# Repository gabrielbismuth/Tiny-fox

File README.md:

# Tiny-fox
Descripción del Proyecto Este repositorio contiene los archivos de diseño de una placa de circuito impreso (PCB) basada en el ESP32 Pico D4. La PCB ha sido diseñada con el objetivo de proporcionar una plataforma flexible y de código abierto para proyectos de IoT, desarrollo de productos y prototipado rápido.

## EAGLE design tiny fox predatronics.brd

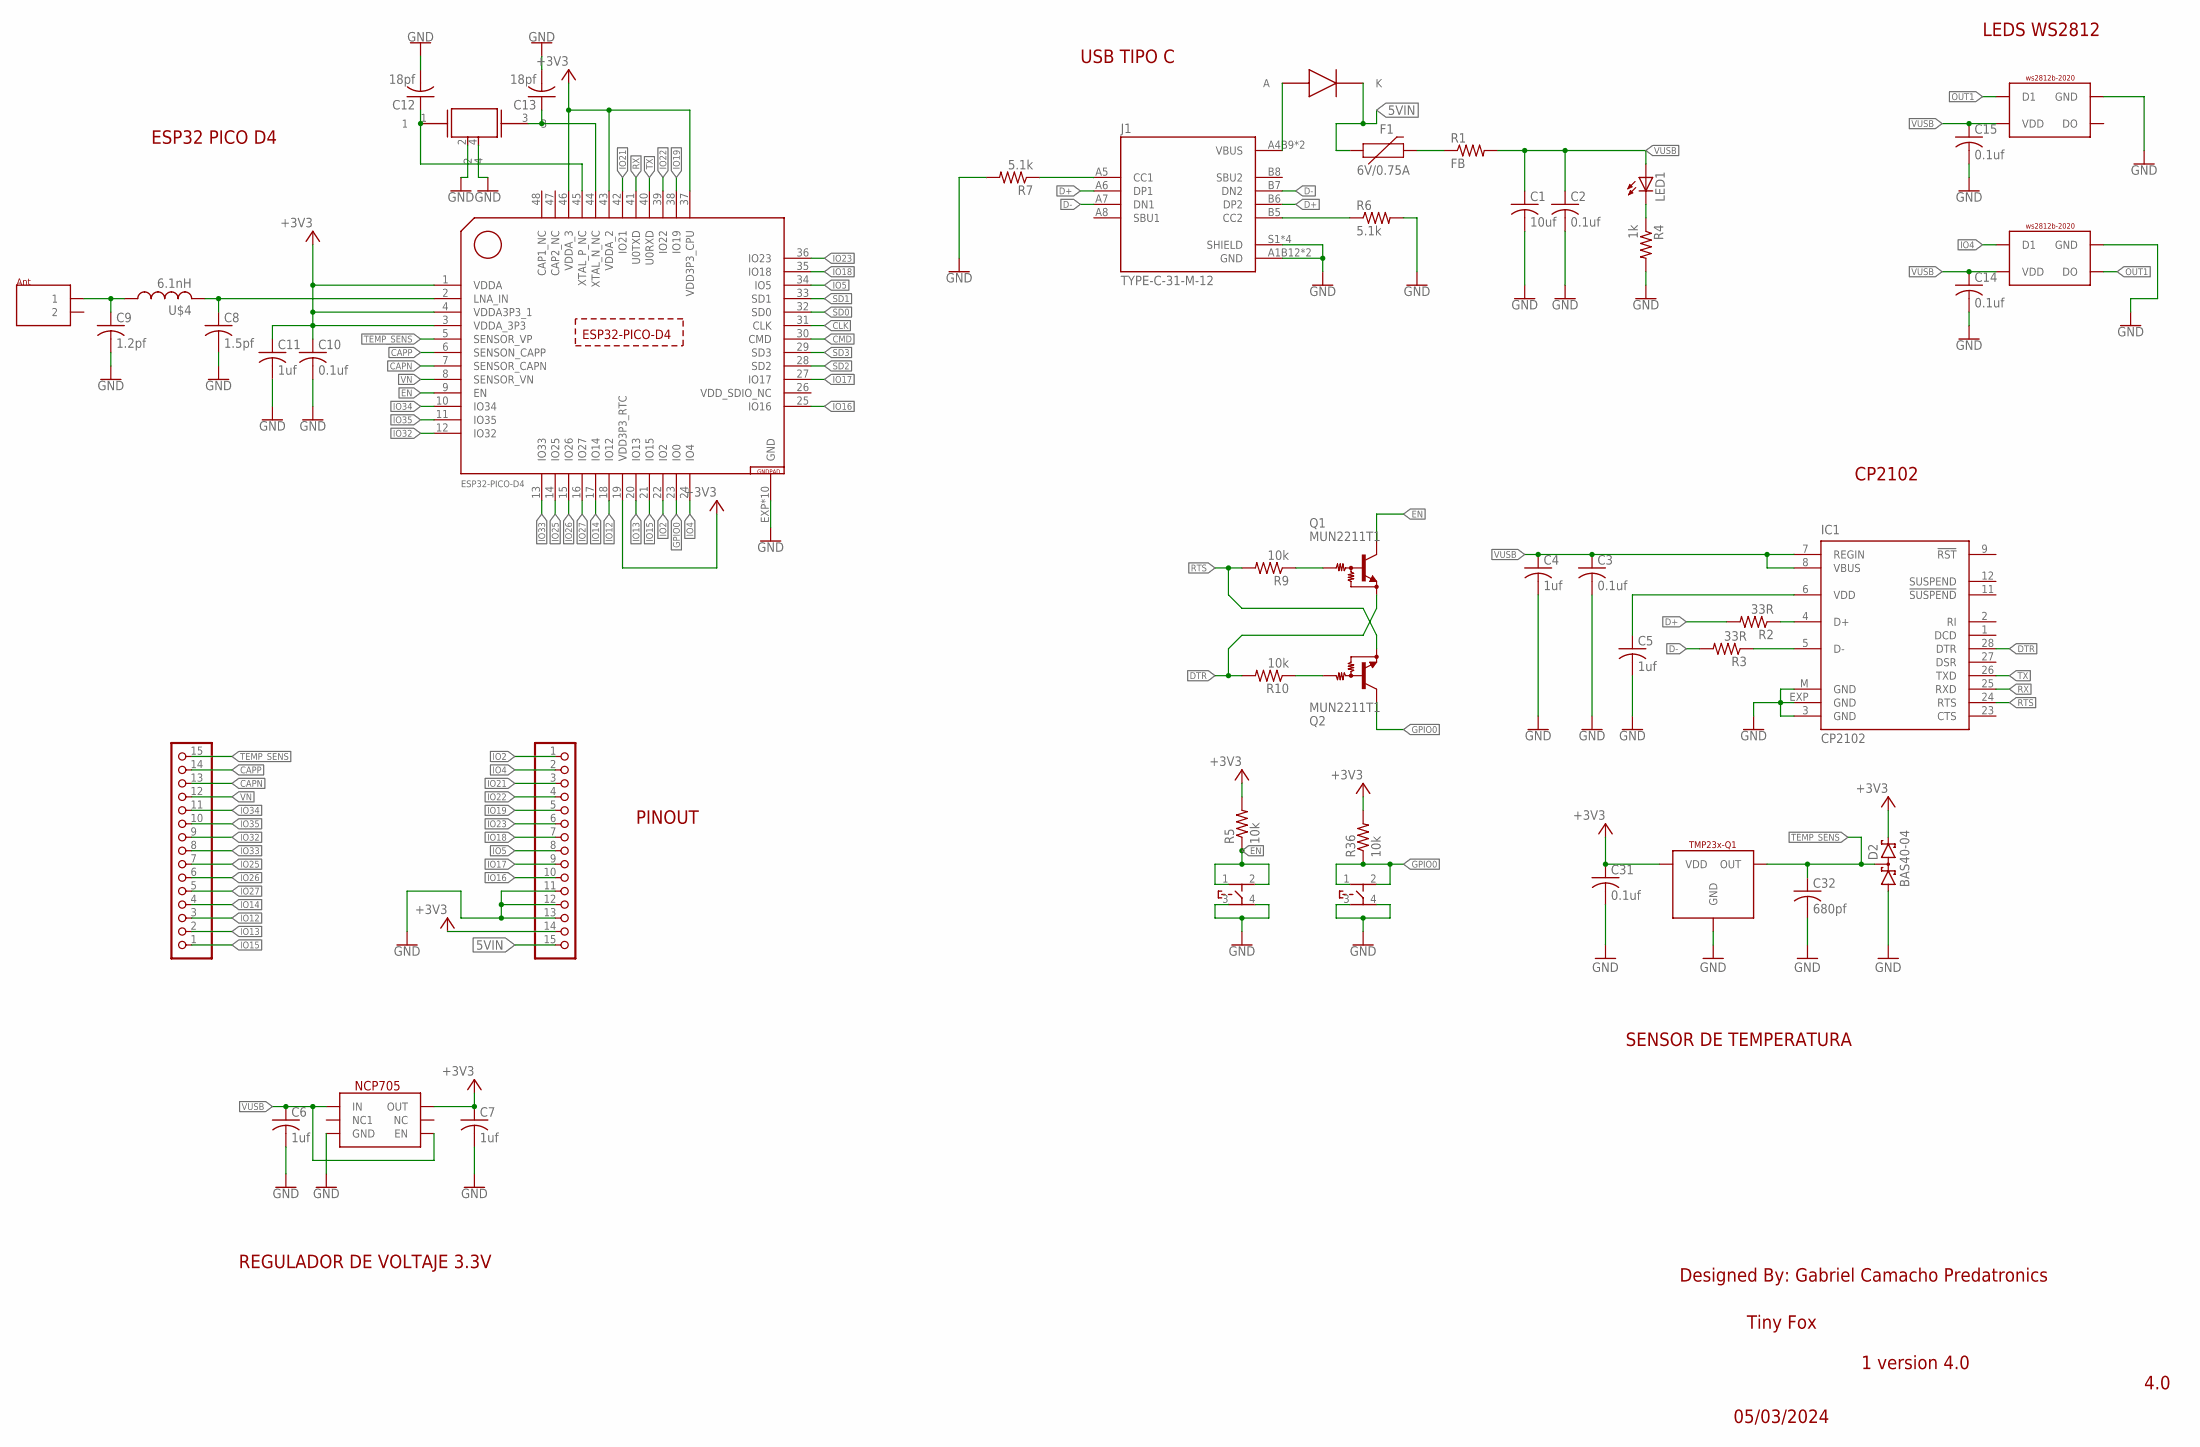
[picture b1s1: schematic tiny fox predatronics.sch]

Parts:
C1: 10uf; C0805
C2, C3, C10, C14, C15, C31: 0.1uf; C0603
C4, C5, C6, C7, C11: 1uf; C0603
C8: 1.5pf; C0402
C9: 1.2pf; C0402
C12, C13: 18pf; C0603
C32: 680pf; C0603
D2: BAS40-04; SOT23
F1: 6V/0.75A; 1206
IC1: CP2102; MLP28
J1: TYPE-C-31-M-12; HRO_TYPE-C-31-M-12
JP1, JP2: PINHD-1X15; 1X15
LED1: LEDCHIPLED_0603; CHIPLED_0603
Q1, Q2: MUN2211T1; SC59-BEC
R1: FB; R0805
R2, R3: 33R; R0603
R4: 1k; R0603
R5, R9, R10, R36: 10k; R0603
R6, R7: 5.1k; R0402
U$1: ESP32-PICO-D4; QFN48
U$2, U$7: WS2812B-2020; 2020
U$3: NCP705; WDFN6
U$4: 6.1nH; RESC0402_M
U$5: CHIP-ANTHENA; ANTHENFOOT
U$6: ECX-32; EXC-32
U$10: RB160MM-50TF; SOD-123FL
U$21: TMP23X-Q1; SOT-23
U$22, U$23: XUNPU; TS-1089S

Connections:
5VIN: F1.1, JP2.15, U$10.K
+3V3: C7.1, C10.1, C11.1, C31.1, D2.2 (C2), JP2.14, R5.2, R36.2, U$1.1 (VDDA), U$1.3 (VDDA_3P3), U$1.4 (VDDA3P3_1), U$1.19 (VDD3P3_RTC), U$1.37 (VDD3P3_CPU), U$1.43 (VDDA_2), U$1.46 (VDDA_3), U$3.OUT, U$21.VDD
CAPN: JP1.13, U$1.7 (SENSOR_CAPN)
CAPP: JP1.14, U$1.6 (SENSON_CAPP)
CLK: U$1.31 (CLK)
CMD: U$1.30 (CMD)
D+: J1.A6 (DP1), J1.B6 (DP2), R2.2
D-: J1.A7 (DN1), J1.B7 (DN2), R3.2
DTR: IC1.28 (DTR), Q1.E, R10.2
EN: Q1.C, R5.1, U$1.9 (EN), U$22.1, U$22.2
GND: C1.2, C2.2, C3.2, C4.2, C5.2, C6.2, C7.2, C8.2, C9.2, C10.2, C11.2, C12.2, C13.2, C14.2, C15.2, C31.2, C32.2, D2.1 (A1), IC1.3 (GND), IC1.EXP (GND), IC1.M (GND), J1.A1B12 (GND), J1.B1A12 (GND), J1.S1 (SHIELD), J1.S2 (SHIELD), J1.S3 (SHIELD), J1.S4 (SHIELD), JP2.11, JP2.12, JP2.13, R4.2, R6.2, R7.2, U$1.EXP (GND), U$1.P$1 (GND), U$1.P$2 (GND), U$1.P$3 (GND), U$1.P$4 (GND), U$1.P$5 (GND), U$1.P$6 (GND), U$1.P$7 (GND), U$1.P$8 (GND), U$1.P$9 (GND), U$2.GND, U$3.GND, U$3.P$7 (GND), U$3.P$8 (GND), U$6.2, U$6.4, U$7.GND, U$21.GND, U$22.3, U$22.4, U$23.3, U$23.4
GPIO0: Q2.C, R36.1, U$1.23 (IO0), U$23.1, U$23.2
IO2: JP2.1, U$1.22 (IO2)
IO4: JP2.2, U$1.24 (IO4), U$2.D1
IO5: JP2.8, U$1.34 (IO5)
IO12: JP1.3, U$1.18 (IO12)
IO13: JP1.2, U$1.20 (IO13)
IO14: JP1.4, U$1.17 (IO14)
IO15: JP1.1, U$1.21 (IO15)
IO16: JP2.10, U$1.25 (IO16)
IO17: JP2.9, U$1.27 (IO17)
IO18: JP2.7, U$1.35 (IO18)
IO19: JP2.5, U$1.38 (IO19)
IO21: JP2.3, U$1.42 (IO21)
IO22: JP2.4, U$1.39 (IO22)
IO23: JP2.6, U$1.36 (IO23)
IO25: JP1.7, U$1.14 (IO25)
IO26: JP1.6, U$1.15 (IO26)
IO27: JP1.5, U$1.16 (IO27)
IO32: JP1.9, U$1.12 (IO32)
IO33: JP1.8, U$1.13 (IO33)
IO34: JP1.11, U$1.10 (IO34)
IO35: JP1.10, U$1.11 (IO35)
unnamed: J1.A4B9 (VBUS), J1.B4A9 (VBUS), U$10.A
unnamed: J1.B5 (CC2), R6.1
unnamed: IC1.4 (D+), R2.1
unnamed: IC1.5 (D-), R3.1
unnamed: C5.1, IC1.6 (VDD)
unnamed: LED1.C, R4.1
unnamed: C9.1, U$4.1, U$5.1
unnamed: C8.1, U$1.2 (LNA_IN), U$4.2
unnamed: C13.1, U$1.44 (XTAL_N_NC), U$6.3
unnamed: Q1.B, R9.1
unnamed: Q2.B, R10.1
unnamed: C12.1, U$1.45 (XTAL_P_NC), U$6.1
unnamed: J1.A5 (CC1), R7.1
unnamed: F1.2, R1.1
OUT1: U$2.DO, U$7.D1
RTS: IC1.24 (RTS), Q2.E, R9.2
RX: IC1.25 (RXD), U$1.41 (U0TXD)
SD0: U$1.32 (SD0)
SD1: U$1.33 (SD1)
SD2: U$1.28 (SD2)
SD3: U$1.29 (SD3)
TEMP_SENS: C32.1, D2.3 (C1A2), JP1.15, U$1.5 (SENSOR_VP), U$21.VOUT (OUT)
TX: IC1.26 (TXD), U$1.40 (U0RXD)
VDD_SDIO_NC: U$1.26 (VDD_SDIO_NC)
VN: JP1.12, U$1.8 (SENSOR_VN)
VUSB: C1.1, C2.1, C3.1, C4.1, C6.1, C14.1, C15.1, IC1.7 (REGIN), IC1.8 (VBUS), LED1.A, R1.2, U$2.VDD, U$3.EN, U$3.IN, U$7.VDD

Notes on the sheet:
Tiny Fox
05/03/2024
Designed By: Gabriel Camacho Predatronics
4.0
1 version 4.0
ESP32 PICO D4
USB TIPO C
LEDS WS2812
CP2102
SENSOR DE TEMPERATURA
REGULADOR DE VOLTAJE 3.3V
PINOUT

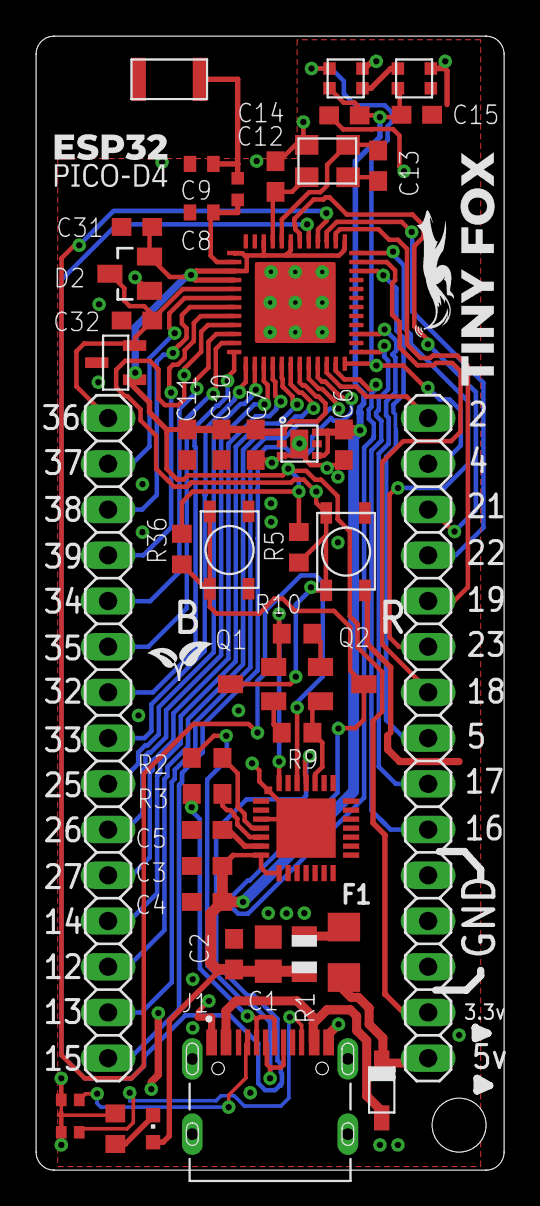
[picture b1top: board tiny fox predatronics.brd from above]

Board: 2 copper layers, 26.0 x 63.0 mm, 47 parts (0 on the bottom side), 52 nets.

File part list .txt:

Partlist

Exported from tiny fox predatronics.sch at 05/03/2024 07:37 p. m.

EAGLE Version 9.5.2 Copyright (c) 1988-2019 Autodesk, Inc.

Assembly variant: 

Part     Value          Device                 Package            Library                 Sheet

C1       10uf           C-USC0805              C0805              rcl                     1
C2       0.1uf          C-USC0603              C0603              rcl                     1
C3       0.1uf          C-USC0603              C0603              rcl                     1
C4       1uf            C-USC0603              C0603              rcl                     1
C5       1uf            C-USC0603              C0603              rcl                     1
C6       1uf            C-USC0603              C0603              rcl                     1
C7       1uf            C-USC0603              C0603              rcl                     1
C8       1.5pf          C-USC0402              C0402              rcl                     1
C9       1.2pf          C-USC0402              C0402              rcl                     1
C10      0.1uf          C-USC0603              C0603              rcl                     1
C11      1uf            C-USC0603              C0603              rcl                     1
C12      18pf           C-USC0603              C0603              rcl                     1
C13      18pf           C-USC0603              C0603              rcl                     1
C14      0.1uf          C-USC0603              C0603              rcl                     1
C15      0.1uf          C-USC0603              C0603              rcl                     1
C31      0.1uf          C-USC0603              C0603              rcl                     1
C32      680pf          C-USC0603              C0603              rcl                     1
D2       BAS40-04       BAS40-04               SOT23              diode                   1
F1       6V/0.75A       PPTC_THREE-QUARTER-AMP 1206               SparkFun-Fuses          1
IC1      CP2102         CP2102                 MLP28              silabs                  1
J1       TYPE-C-31-M-12 TYPE-C-31-M-12         HRO_TYPE-C-31-M-12 TYPE-C-31-M-12          1
JP1                     PINHD-1X15             1X15               pinhead                 1
JP2                     PINHD-1X15             1X15               pinhead                 1
LED1                    LEDCHIPLED_0603        CHIPLED_0603       adafruit                1
Q1       MUN2211T1      MUN2211T1              SC59-BEC           transistor-npn          1
Q2       MUN2211T1      MUN2211T1              SC59-BEC           transistor-npn          1
R1       FB             R-US_R0805             R0805              audio amplifier example 1
R2       33R            R-US_R0603             R0603              resistor                1
R3       33R            R-US_R0603             R0603              resistor                1
R4       1k             R-US_R0603             R0603              resistor                1
R5       10k            R-US_R0603             R0603              adafruit                1
R6       5.1k           R-US_R0402             R0402              rcl                     1
R7       5.1k           R-US_R0402             R0402              rcl                     1
R9       10k            R-US_R0603             R0603              resistor                1
R10      10k            R-US_R0603             R0603              resistor                1
R36      10k            R-US_R0603             R0603              adafruit                1
U$1      ESP32-PICO-D4  ESP32-PICO-D4          QFN48              esp32-pico-d4           1
U$2      WS2812B-2020   WS2812B-2020           2020               ws2812b-2020            1
U$3      NCP705         NCP705                 WDFN6              NCP705                  1
U$4      6.1nH          INDUCTOR_0402_M        RESC0402_M         Nordic_nRF              1
U$5      CHIP-ANTHENA   CHIP-ANTHENA           ANTHENFOOT         NN01-110                1
U$6      ECX-32         ECX-32                 EXC-32             cristal                 1
U$7      WS2812B-2020   WS2812B-2020           2020               ws2812b-2020            1
U$10     RB160MM-50TF   RB160MM-50TF           SOD-123FL          RB160MM-50TF            1
U$21     TMP23X-Q1      TMP23X-Q1              SOT-23             TMP23x-Q1               1
U$22     XUNPU          XUNPU                  TS-1089S           TS-1089S-02526          1
U$23     XUNPU          XUNPU                  TS-1089S           TS-1089S-02526          1

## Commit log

2024-03-06 Add files via upload
    ¡Hola! Claro que sí, puedo ayudarte con eso. Aquí tienes una propuesta de descripción para tu repositorio de GitHub:
    Descripción del Proyecto
    Este repositorio contiene los archivos de diseño de una placa de circuito impreso (PCB) basada en el ESP32 Pico D4. La PCB ha sido diseñada con el objetivo de proporcionar una plataforma flexible y d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
    Características Principales:
    ESP32 Pico D4: La placa está equipada con un ESP32 Pico D4, un potente microcontrolador de bajo consumo de energía que combina Wi-Fi y Bluetooth.
    Diseño Abierto: Todos los archivos de diseño, incluido

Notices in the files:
parts and their libraries:
SparkFun-Fuses: Licensing: Creative Commons ShareAlike 4.0 International - https://creativecommons.org/licenses/by-sa/4.0
